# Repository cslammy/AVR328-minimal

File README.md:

# AVR328-minimal
minimalist develop board centered around AVR328P or AVR328 microcontrollers.  
Includes Eagle SCM and BRD files, gerber, BOM, sample C code

You can fab this project at PCBWay (who sponsors my blog): https://www.pcbway.com/project/shareproject/Minimal_Atmel_328P_MCU.html

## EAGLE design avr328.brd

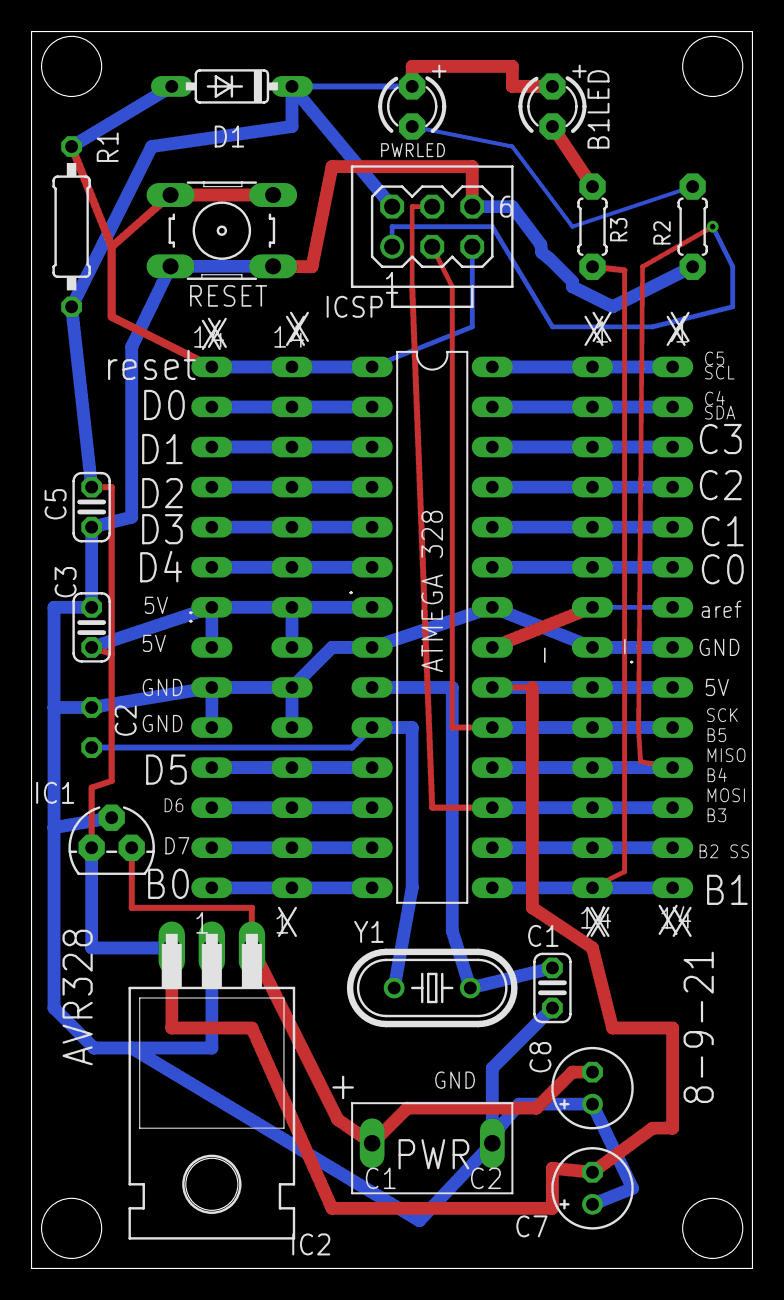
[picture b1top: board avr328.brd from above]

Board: 2 copper layers, 45.7 x 78.4 mm, 23 parts (1 on the bottom side), 29 nets.

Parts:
-: 14_PIN_CONN
., .-, ..: 14_PIN_CONN
B1LED: LED3MM
C1, C2: 22pF; C025-024X044
C3, C5: 0.1uF; C025-024X044
C7, C8: 10uF; E2-5
D1: DO35-7
IC1: 7805L; TO92
IC2: 7805T; TO220H
ICSP: MA03-2
PWR: PWR; 2_PIN_SCREW_CONN
PWRLED: LED3MM
R1: 10K; 0207/10
R2: 2K; 0204/5
R3: 1K; 0204/5
RESET: B3F-10XX
U$1: ATMEGA_328_DIL
Y1: HC49U-V

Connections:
+5V: -.9, ..7, ..8, .-.9, ...7, ...8, B1LED.A, C3.2, C5.2, C7.-, D1.C, IC1.1, IC2.3, ICSP.2, PWRLED.A, R1.1, U$1.7, U$1.20
AREF: -.7, .-.7, U$1.21
GND: -.8, ..5, ..6, .-.8, ...5, ...6, C1.1, C2.1, C3.1, C5.1, C7.+, C8.+, IC1.2, IC2.2, ICSP.6, PWR.P$2, R2.1, RESET.1, RESET.2, U$1.8, U$1.22
MISO: -.11, .-.11, ICSP.1, U$1.18
MOSI: -.12, .-.12, ICSP.4, U$1.17
unnamed: ..14, ...14, D1.A, ICSP.5, R1.2, RESET.3, RESET.4, U$1.1
unnamed: C1.2, U$1.9, Y1.2
unnamed: C2.2, U$1.10, Y1.1
unnamed: ..13, ...13, U$1.2
unnamed: ..12, ...12, U$1.3
unnamed: ..11, ...11, U$1.4
unnamed: C8.-, IC1.3, IC2.1, PWR.P$1
unnamed: ..9, ...9, U$1.6
unnamed: B1LED.K, R3.1
unnamed: -.1, .-.1, U$1.28
unnamed: -.2, .-.2, U$1.27
unnamed: -.3, .-.3, U$1.26
unnamed: -.4, .-.4, U$1.25
unnamed: -.5, .-.5, U$1.24
unnamed: -.6, .-.6, U$1.23
unnamed: -.14, .-.14, R3.2, U$1.15
unnamed: -.13, .-.13, U$1.16
unnamed: PWRLED.K, R2.2
unnamed: ..1, ...1, U$1.14
unnamed: ..2, ...2, U$1.13
unnamed: ..3, ...3, U$1.12
unnamed: ..4, ...4, U$1.11
unnamed: ..10, ...10, U$1.5
SCK: -.10, .-.10, ICSP.3, U$1.19

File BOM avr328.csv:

"Part";"Value";"Device";"Package";"Description";"MF";"MPN";"OC_FARNELL";"OC_NEWARK";"POPULARITY";"SPICEPREFIX";
"-";"";"14_PIN_CONN";"14_PIN_CONN";"";"";"";"";"";"";"";
".";"";"14_PIN_CONN";"14_PIN_CONN";"";"";"";"";"";"";"";
".-";"";"14_PIN_CONN";"14_PIN_CONN";"";"";"";"";"";"";"";
"..";"";"14_PIN_CONN";"14_PIN_CONN";"";"";"";"";"";"";"";
"B1LED";"";"LED3MM";"LED3MM";"LED";"";"";"";"";"";"";
"C1";"22pF";"C-EU025-024X044";"C025-024X044";"CAPACITOR, European symbol";"";"";"";"";"";"";
"C2";"22pF";"C-EU025-024X044";"C025-024X044";"CAPACITOR, European symbol";"";"";"";"";"";"";
"C3";"0.1uF";"C-EU025-024X044";"C025-024X044";"CAPACITOR, European symbol";"";"";"";"";"";"";
"C5";"0.1uF";"C-EU025-024X044";"C025-024X044";"CAPACITOR, European symbol";"";"";"";"";"";"";
"C7";"10uF";"CPOL-USE2-5";"E2-5";"POLARIZED CAPACITOR, American symbol";"";"";"";"";"7";"C";
"C8";"10uF";"CPOL-USE2-5";"E2-5";"POLARIZED CAPACITOR, American symbol";"";"";"";"";"7";"C";
"D1";"";"1N4148DO35-7";"DO35-7";"DIODE";"";"";"";"";"58";"";
"IC1";"7805L";"7805L";"TO92";"Positive VOLTAGE REGULATOR";"";"";"";"";"";"";
"IC2";"7805T";"7805T";"TO220H";"Positive VOLTAGE REGULATOR";"";"";"";"";"";"";
"ICSP";"";"MA03-2";"MA03-2";"PIN HEADER";"";"";"unknown";"unknown";"15";"";
"PWR";"PWR";"2_PIN_SCREW_CONN";"2_PIN_SCREW_CONN";"";"";"";"";"";"";"";
"PWRLED";"";"LED3MM";"LED3MM";"LED";"";"";"";"";"";"";
"R1";"10K";"R-EU_0207/10";"0207/10";"RESISTOR, European symbol";"";"";"";"";"";"";
"R2";"2K";"R-US_0204/5";"0204/5";"RESISTOR, American symbol";"";"";"";"";"";"";
"R3";"330";"R-US_0204/5";"0204/5";"RESISTOR, American symbol";"";"";"";"";"";"";
"RESET";"";"SPST_TACT-EVQQ2";"EVQ-Q2";"SMT 6mm switch, EVQQ2 series";"";"";"";"";"";"";
"U$1";"ATMEGA_328_DIL";"ATMEGA_328_DIL";"ATMEGA_328_DIL";"";"";"";"";"";"";"";
"Y1";"";"CRYSTALHC49UV";"HC49U-V";"Various standard crystals. Proven footprints. Spark Fun Electronics SKU : COM-00534";"";"";"";"";"";"";

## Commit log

2021-04-24 Zip of Studio 7 AVR blink sketch
    See this blog post
    https://audiodiwhy.blogspot.com/2021/04/minimalist-atmel-328-development-board.html
2021-04-24 Eagle Board and schmeatic file
    See blog post https://audiodiwhy.blogspot.com/2021/04/minimalist-atmel-328-development-board.html
2021-04-24 Gerber files for AVR minimalist dev board
    See this blog post for more information: https://audiodiwhy.blogspot.com/2021/04/minimalist-atmel-328-development-board.html
2021-08-06 Added BOM file
    Details in this blog post: http://audiodiwhy.blogspot.com/2021/04/minimalist-atmel-328-development-board.html
2021-10-31 added pin legends to both sides of board
    Before the pin designations were on top side of the board only, same as the parts. I added designations to the bottom as well so you don'[t have to keep flipping the board over to see what pin you ar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
2021-10-31 Changed B1 LED polarity
2021-10-31 Delete avr328.brd
    Deprecated
2021-10-31 Delete avr328.sch
    Deprecated
2021-10-31 Rename avr328 8-9-21.brd to avr328.brd
2021-10-31 Delete avr328 8-9-21.sch
    Can't rename file so I will repost! arrrg!
2021-10-31 Changed polarity of B1 LED
2021-10-31 Rename BOM avr328 5-29-21.csv to BOM avr328.csv
    I use dates on my sch and brd files but that doesn't work with github....

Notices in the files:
parts and their libraries:
SparkFun-FreqCtrl: Licensing: CC v3.0 Share-Alike You are welcome to use this library for commercial purposes.
